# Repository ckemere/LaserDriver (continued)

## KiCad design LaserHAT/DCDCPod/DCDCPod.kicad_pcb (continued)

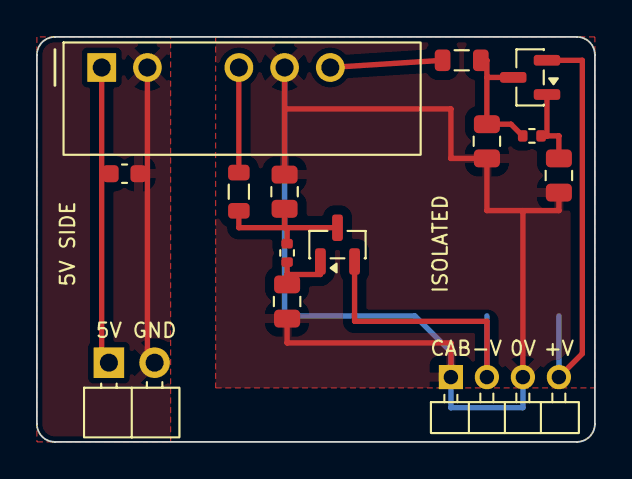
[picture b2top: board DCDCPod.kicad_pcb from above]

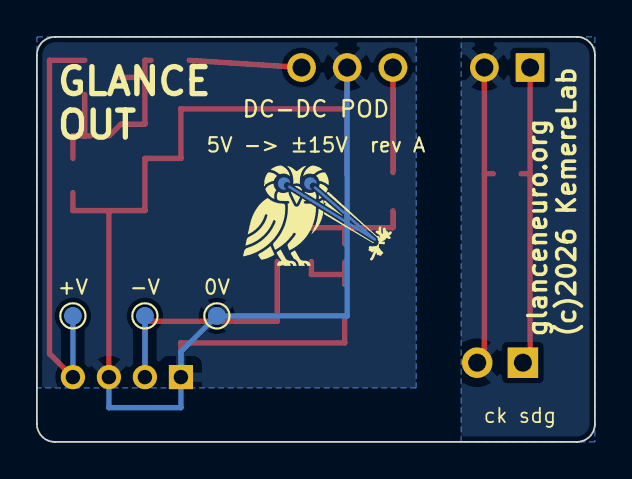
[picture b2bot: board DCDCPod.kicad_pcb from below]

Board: 2 copper layers, 31.0 x 22.5 mm, 18 parts (4 on the bottom side), 11 nets.

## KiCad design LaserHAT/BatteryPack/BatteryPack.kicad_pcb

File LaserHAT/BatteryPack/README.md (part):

# BatteryPack — ±V battery board for the e-stim module (rev D: series packs, floating charger)

Rev D, 2026-10-28.  One 100 × 100 mm board carries two off-the-shelf 4S hobby packs (any LiPo or Li-ion pack with the
standard JST-XH 5-pin balance plug and an XT60 discharge plug, 850–1550 mAh class, about 70–76 × 35 × 30–37 mm) strapped
to its underside, permanently in series, and gives the e-stim module +V / 0 V / −V (12.0–16.8 V per rail) on a 4-pin
JST-PH.  One USB-C PD charger floats on its own ground and a relay, run by a small MCU, switches it between the packs; one
toggle does ON / OFF.  2-layer, JLC assembled (toggle, XH and PH sockets, XT60s and the relay through-hole).

Rev C (commit `8b583b4`) charged the packs in parallel through a RUN / OFF / CHARGE toggle.  That made one half of the board
jump by a pack voltage between the modes, needed a PTC link and an equalising rule for mismatched packs, and left no single
reference for a ground pour.  Rev D fixes the pack topology and moves all the switching into the charger.  Rev B
(`6fa6e9d`) was a 4S 18650 board with clips, two of them stacked.  The output cable to the module is unchanged except that
its pin 4 is now an interlock.

Files: `gen_schematic.py` + `sch_parts.py` + `sch_symbols.py` (+ `sch_engine.py`) generate `BatteryPack.kicad_sch`
(deterministic UUIDs, like the e-stim module); `tools/netcheck.py` proves the drawing matches `sch_parts.py`;
`tools/make_bom.py` writes `bom_BatteryPack.csv`; `tools/make_footprints.py` writes `battpack.pretty/` (toggle, relay,
opto; the clip footprint is kept for rev B).  Board: `tools/board_init.py` (once), `tools/pcb_sync.py` (footprints and
nets from the netlist), `tools/place.py` (outline, slots, holes, placement, silk; idempotent) and `tools/autoroute.py`
(rip-up, stubs out of pads narrower than their net class, Freerouting headless through DSN/SES, stub clean-up, DRC) built
it — the user is remote, so the layout is scripted rather than hand-placed like the other boards.  Hand edits in pcbnew
are fine afterwards; re-running `place.py` + `autoroute.py` discards them.  `tools/stamp_fields.py` puts the LCSC codes on
the footprints, `tools/make_fab.py` writes `../fab/BatteryPack/` (gerbers, JLC BOM + CPL).  `firmware/` is the charge
controller's program (see below).

## What is on it

| Block | Parts | Notes |
|---|---|---|
| Pack sockets | per pack an XT60 and a JST-XH: J7 / J5 (pack A, −V side), J8 / J6 (pack B, +V side); XT60 = Amass XT60PW-M horizontal (C98732, ext), XH = JST S5B-XH-A-1 right-angle (C163038, ext) | the XT60 discharge plug carries the run and charge current (J7 = GND / 0V, J8 = 0V / +BATB; the plug is keyed, the footprint silk marks + and −); the balance plug gives the cell taps (XH pin 1 = black = pack negative, 2–4 = taps, 5 = pack positive; pins 1 and 5 parallel the XT60).  J5 = GND, C1, C2, C3, 0V; J6 = 0V, B1, B2, B3, +BATB.  **0V = pack A's positive = pack B's negative = the output reference, always.**  A pack with an XT30 lead needs an XT30-to-XT60 adapter |
| Balancers | pack A: U6–U9 HY2213-BB3A (C113632, ext), Q7–Q10 AO3400A, R35–R38 100 R 1206, R31–R34, C12–C15; pack B: U10–U13, Q15–Q18, R62–R65, R58–R61, C16–C19 | 42 mA bleed above 4.200 V, release 4.19 V, 2.5 µA standing, per cell of both packs |
| Toggle | SW1 MTS-202 DPDT ON-ON (C55159891, ext; **JLC stock 195 on 2026-10-28**) | **ON / OFF**.  Pole 1 (common EN_A): ON → 0V.  Pole 2 (common EN_B): ON → +BATB.  OFF opens both: outputs off, gauges dark (R40 / R82 hold the enables low) |
| +V chain (pack B) | F1 100 mA PTC MF-MSMF010-2 (C12430, ext), Q1 AO3401A, R1/R2 100k, Q22 2N7002, R81 1M, U15B (LM393), R53 1M | +BATB → F1 → +SW → Q1 → +OUT (J3.1).  Q22 pulls Q1's gate low while ENB_G (= EN_B through R81) is high **and its source, J3.4, is at 0V** — the module's plug straps pin 4 to pin 2, so +V can only appear with 0V connected.  U15B pulls ENB_G low below 12.0 V (back above 12.8 V), the opto U17 pulls it low while a brick is plugged in |
| −V chain (pack A) | F2 100 mA PTC, Q11 AO3400A (N, in pack A's negative), R39/R40 100k, U2B (LM393), R11 470k, Q14 + D1 (ON) | GND → F2 → Q11 → −V (J3.3).  Q11's gate is pack A / 2 from EN_A (= 0V when ON); U2B pulls it low below 12.0 V, back on above 12.9 V.  −V alone is harmless to the module (nothing in it conducts without 0V), so chain A is not interlocked.  Q14 lights D1 while Q11 conducts |
| Gauge rails | Q20 AO3401A + R77/R78 + Q21 2N7002 + R79/R80 (+G = 0V through Q20); Q23 + R83/R84 + Q24 (+GB = +BATB through Q23) | both rails follow EN_A / EN_B only: the gauges show whenever the toggle is ON, charging or not |
| Gauges | pack A: U3 CJ431, R3–R10, U1/U2 LM393, D2–D4 + R13–R15 on +G; pack B: U16, R45–R52, U14/U15, D12–D14 + R55–R57 on +GB, D11 + R54 ON from +OUT | per pack: green ≥ 15.9 V, green ≥ 15.1 V, yellow ≥ 14.3 V, ~1 mA each (the ladder's R4 / R46 is 6.2k now that the rail is the pack itself, not the pack − 0.25 V) |
| Charging interlock | U17 EL817S1 opto (C2912100, ext), R76 10k | LED from the island's VBUS; transistor holds ENB_G at 0V → +V off (and the module's fault line reports it) whenever a brick is in, so the brick's mains leakage can never reach the electrode |
| **Charger island** (floats on CGND) | J1 USB-C (C165948, ext), U4 CH224A (C42459160, ext) + C3 + R24 120k, U18 TLV76033 LDO (C2683368, ext) + C22/C23, **Q13 AO3401A VBUS switch** + R43/R44 + C28 10n (0.5 ms soft start) + Q12 2N7002 + R42, U5 CN3704 (C51659, ext), Q6 AO3401A, D7/D8 SS34, L1 33 µH (C408454, ext; CN3704 table 2 for 1 A at 20 V in; LCSC's own site does not list this code but JLC's parts search does, 10 k in stock, as for the 22 µH C408453 before), R25+R26 0.2 R, C4–C11, R27, RT1 NTC (C13564, ext), R28/R29 10k | PD brick negotiated to 20 V (the CH224A's DP / DM stay open: the USB data lines belong to the MCU).  Q13 passes VBUS to the charger only while the MCU drives CHG_EN; the charger's output +CHG / CGND goes to the relay.  1 A CC into one pack at a time, 16.8 V ±1 % CV, termination 92 mA, trickle 150 mA below 11.2 V, re-charge below 16.0 V, 18.1 V over-voltage cut, NTC stops it hot / cold.  The island is the only part of the board whose potential moves (it rides on GND or on 0V); the brick is mains-isolated, so that is fine.  **Up to 2 A:** R25 + R26 = 0.1 R, L1 20 µH, a 45 W brick (the HFD2's contacts are rated 2 A) |
| Relays | K1 Omron G6S-2 DC12 (C1525289, ext), R86 680 R 1206, Q19 2N7002, R85 100k, D19 1N4148W; **K2 LINK**: the same relay (R88, Q25, R87, D20), both poles NO in series with the island's +CHG and CGND | 12 V coils (1028 Ω) fed from VBUS through 680 R: 11.7 mA, 12 V on the coil at 20 V, must-operate 9 V (the 24 V HFD2 of the first draft had a ≤ 18 V pick-up against a 20 V bus minus cable drop: no margin).  Pin 1 = coil +, 12 = coil −; D19 flyback across the coil; R85 holds Q19 off while the MCU is in reset / DFU.  DPDT 2 A: released = pack A (NC 3 / 10: +CHG → 0V, CGND → GND), energised = pack B (NO 5 / 8: +CHG → +BATB, CGND → 0V).  Only ever switched with the charger off **and with K2 open**: a DPDT's two poles are not guaranteed to transfer together, and with the island still tied to one pack the mismatched intermediate states (+CHG on +BATB with CGND on GND, or both on 0V) would put 33.6 V across the charger (C7 / C8 25 V, CN3704 BAT 28 V abs max) or short C7 / C8 through the contacts; so the MCU opens K2, moves K1, closes K2 (30 ms each; G6S-2 operate / release ≤ 5 ms).  K2 is also open whenever the MCU is unpowered or idle, so the island is off both packs then (no idle drain, nothing lifted by leakage through D7 / Q6) |
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
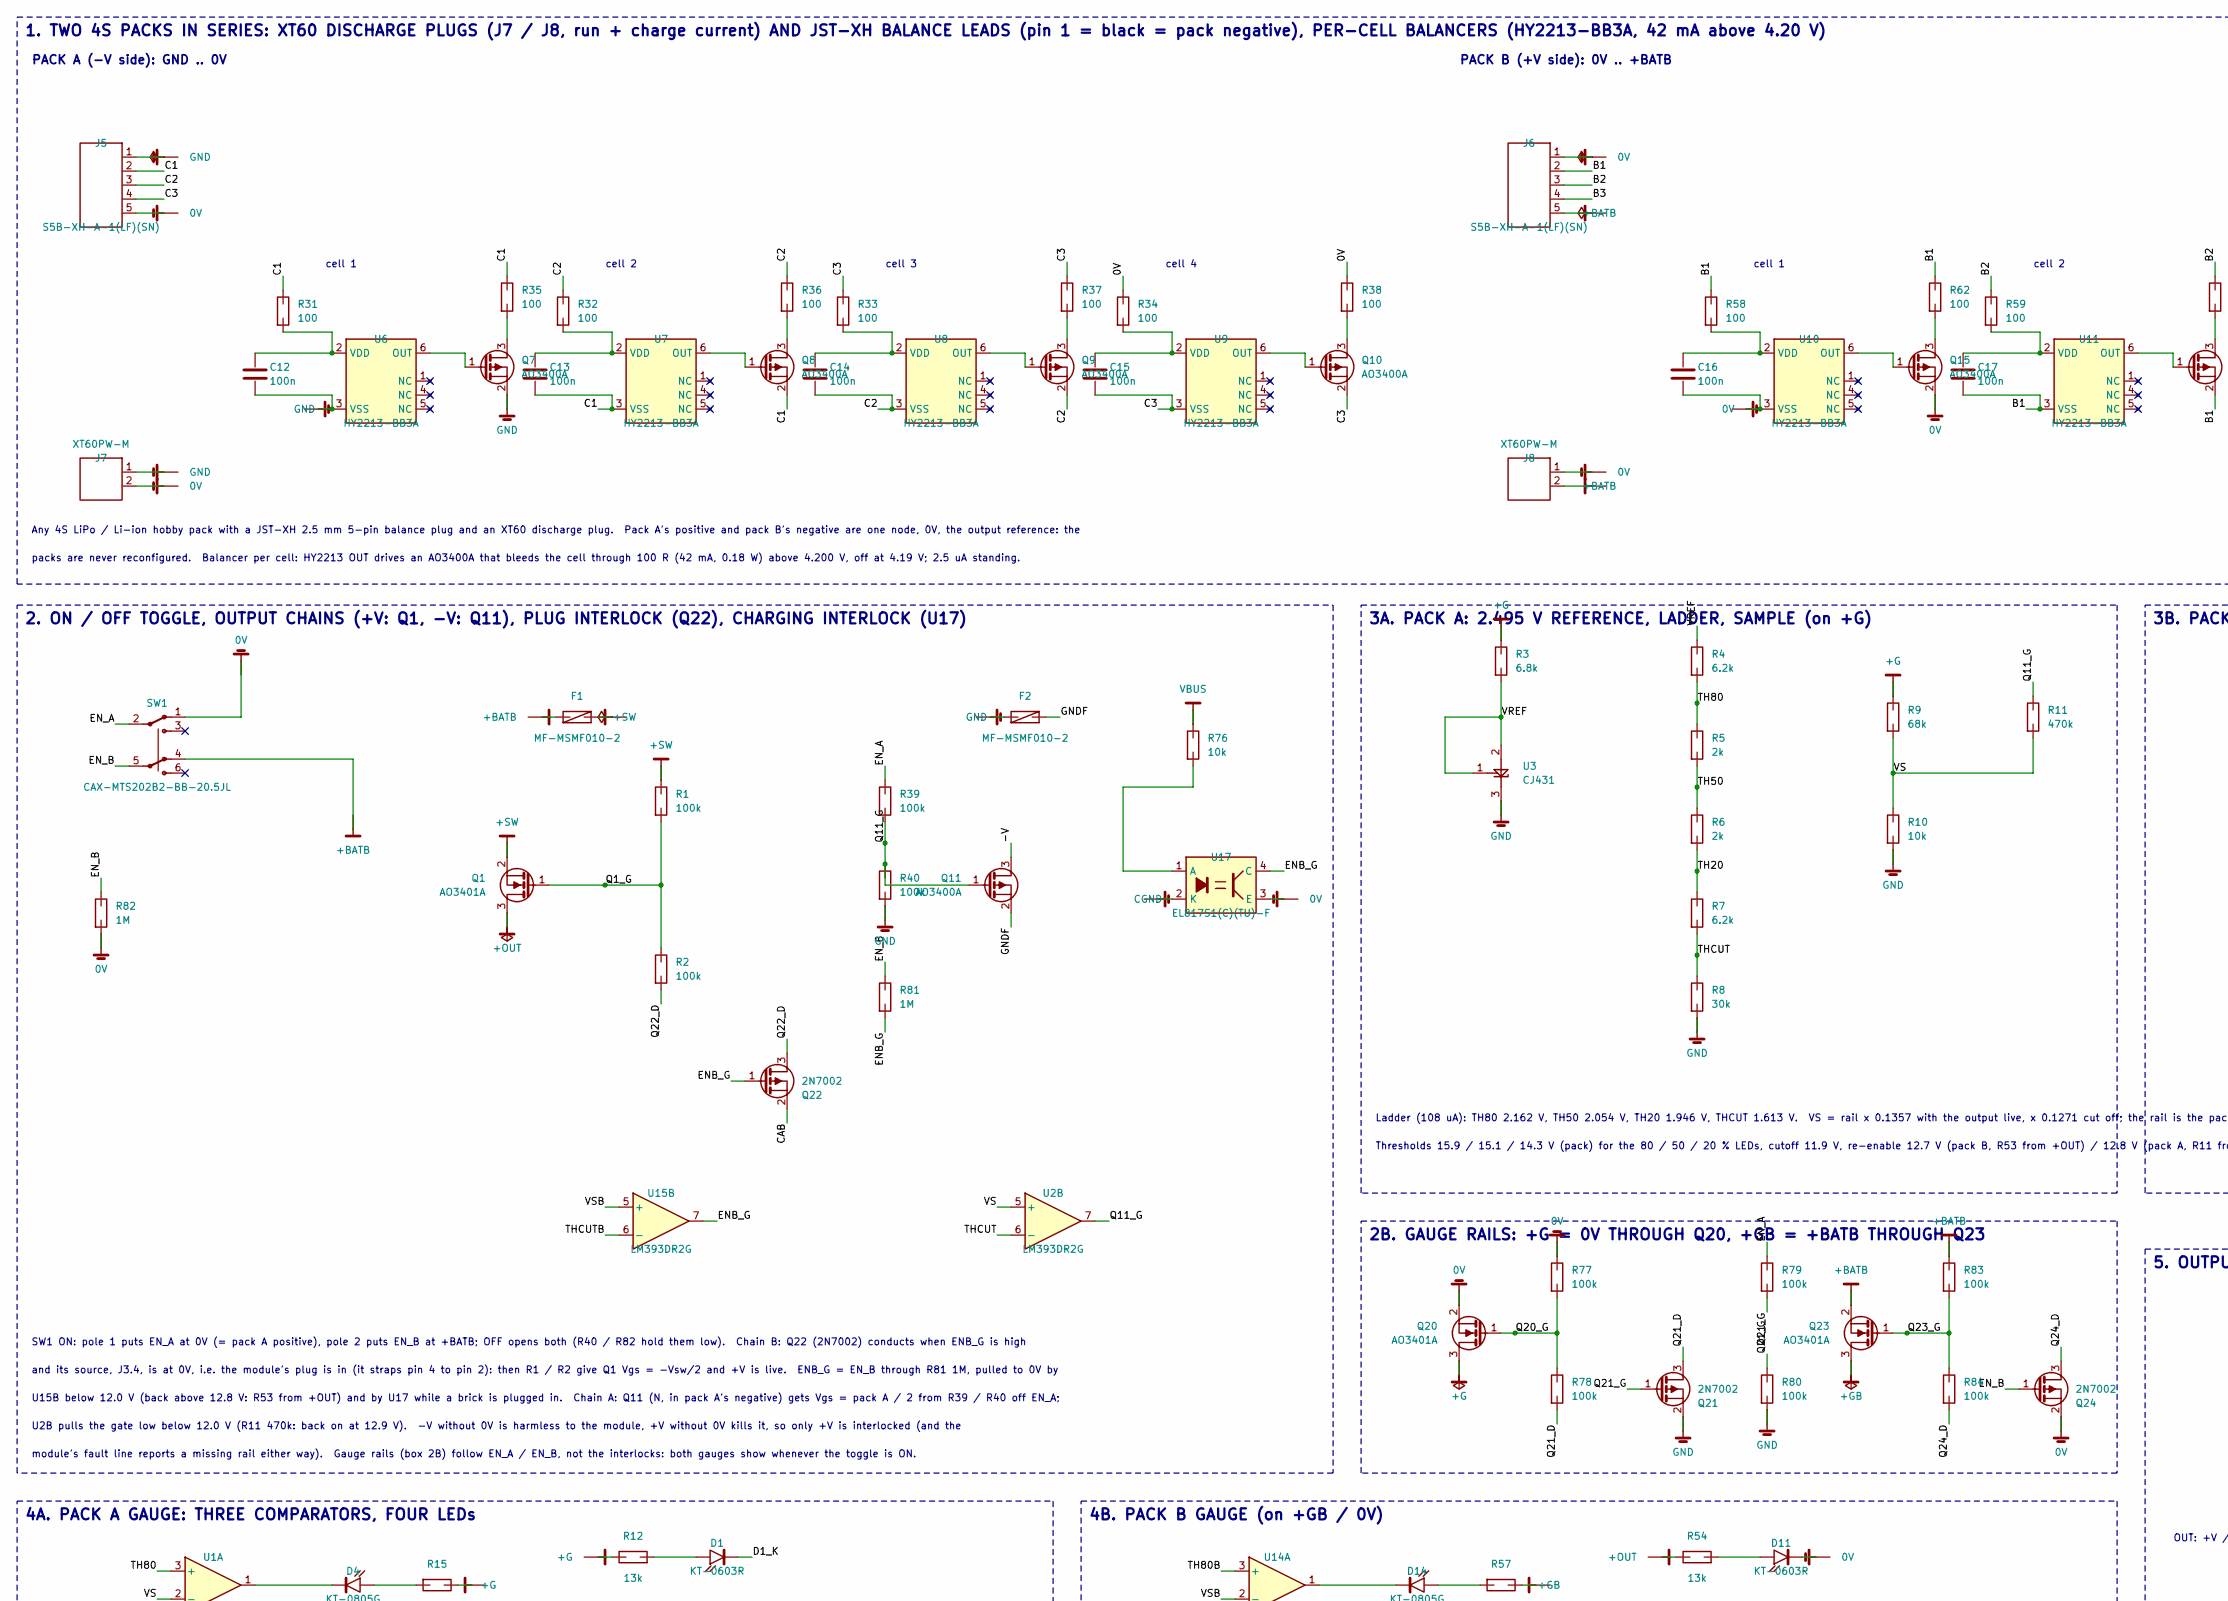
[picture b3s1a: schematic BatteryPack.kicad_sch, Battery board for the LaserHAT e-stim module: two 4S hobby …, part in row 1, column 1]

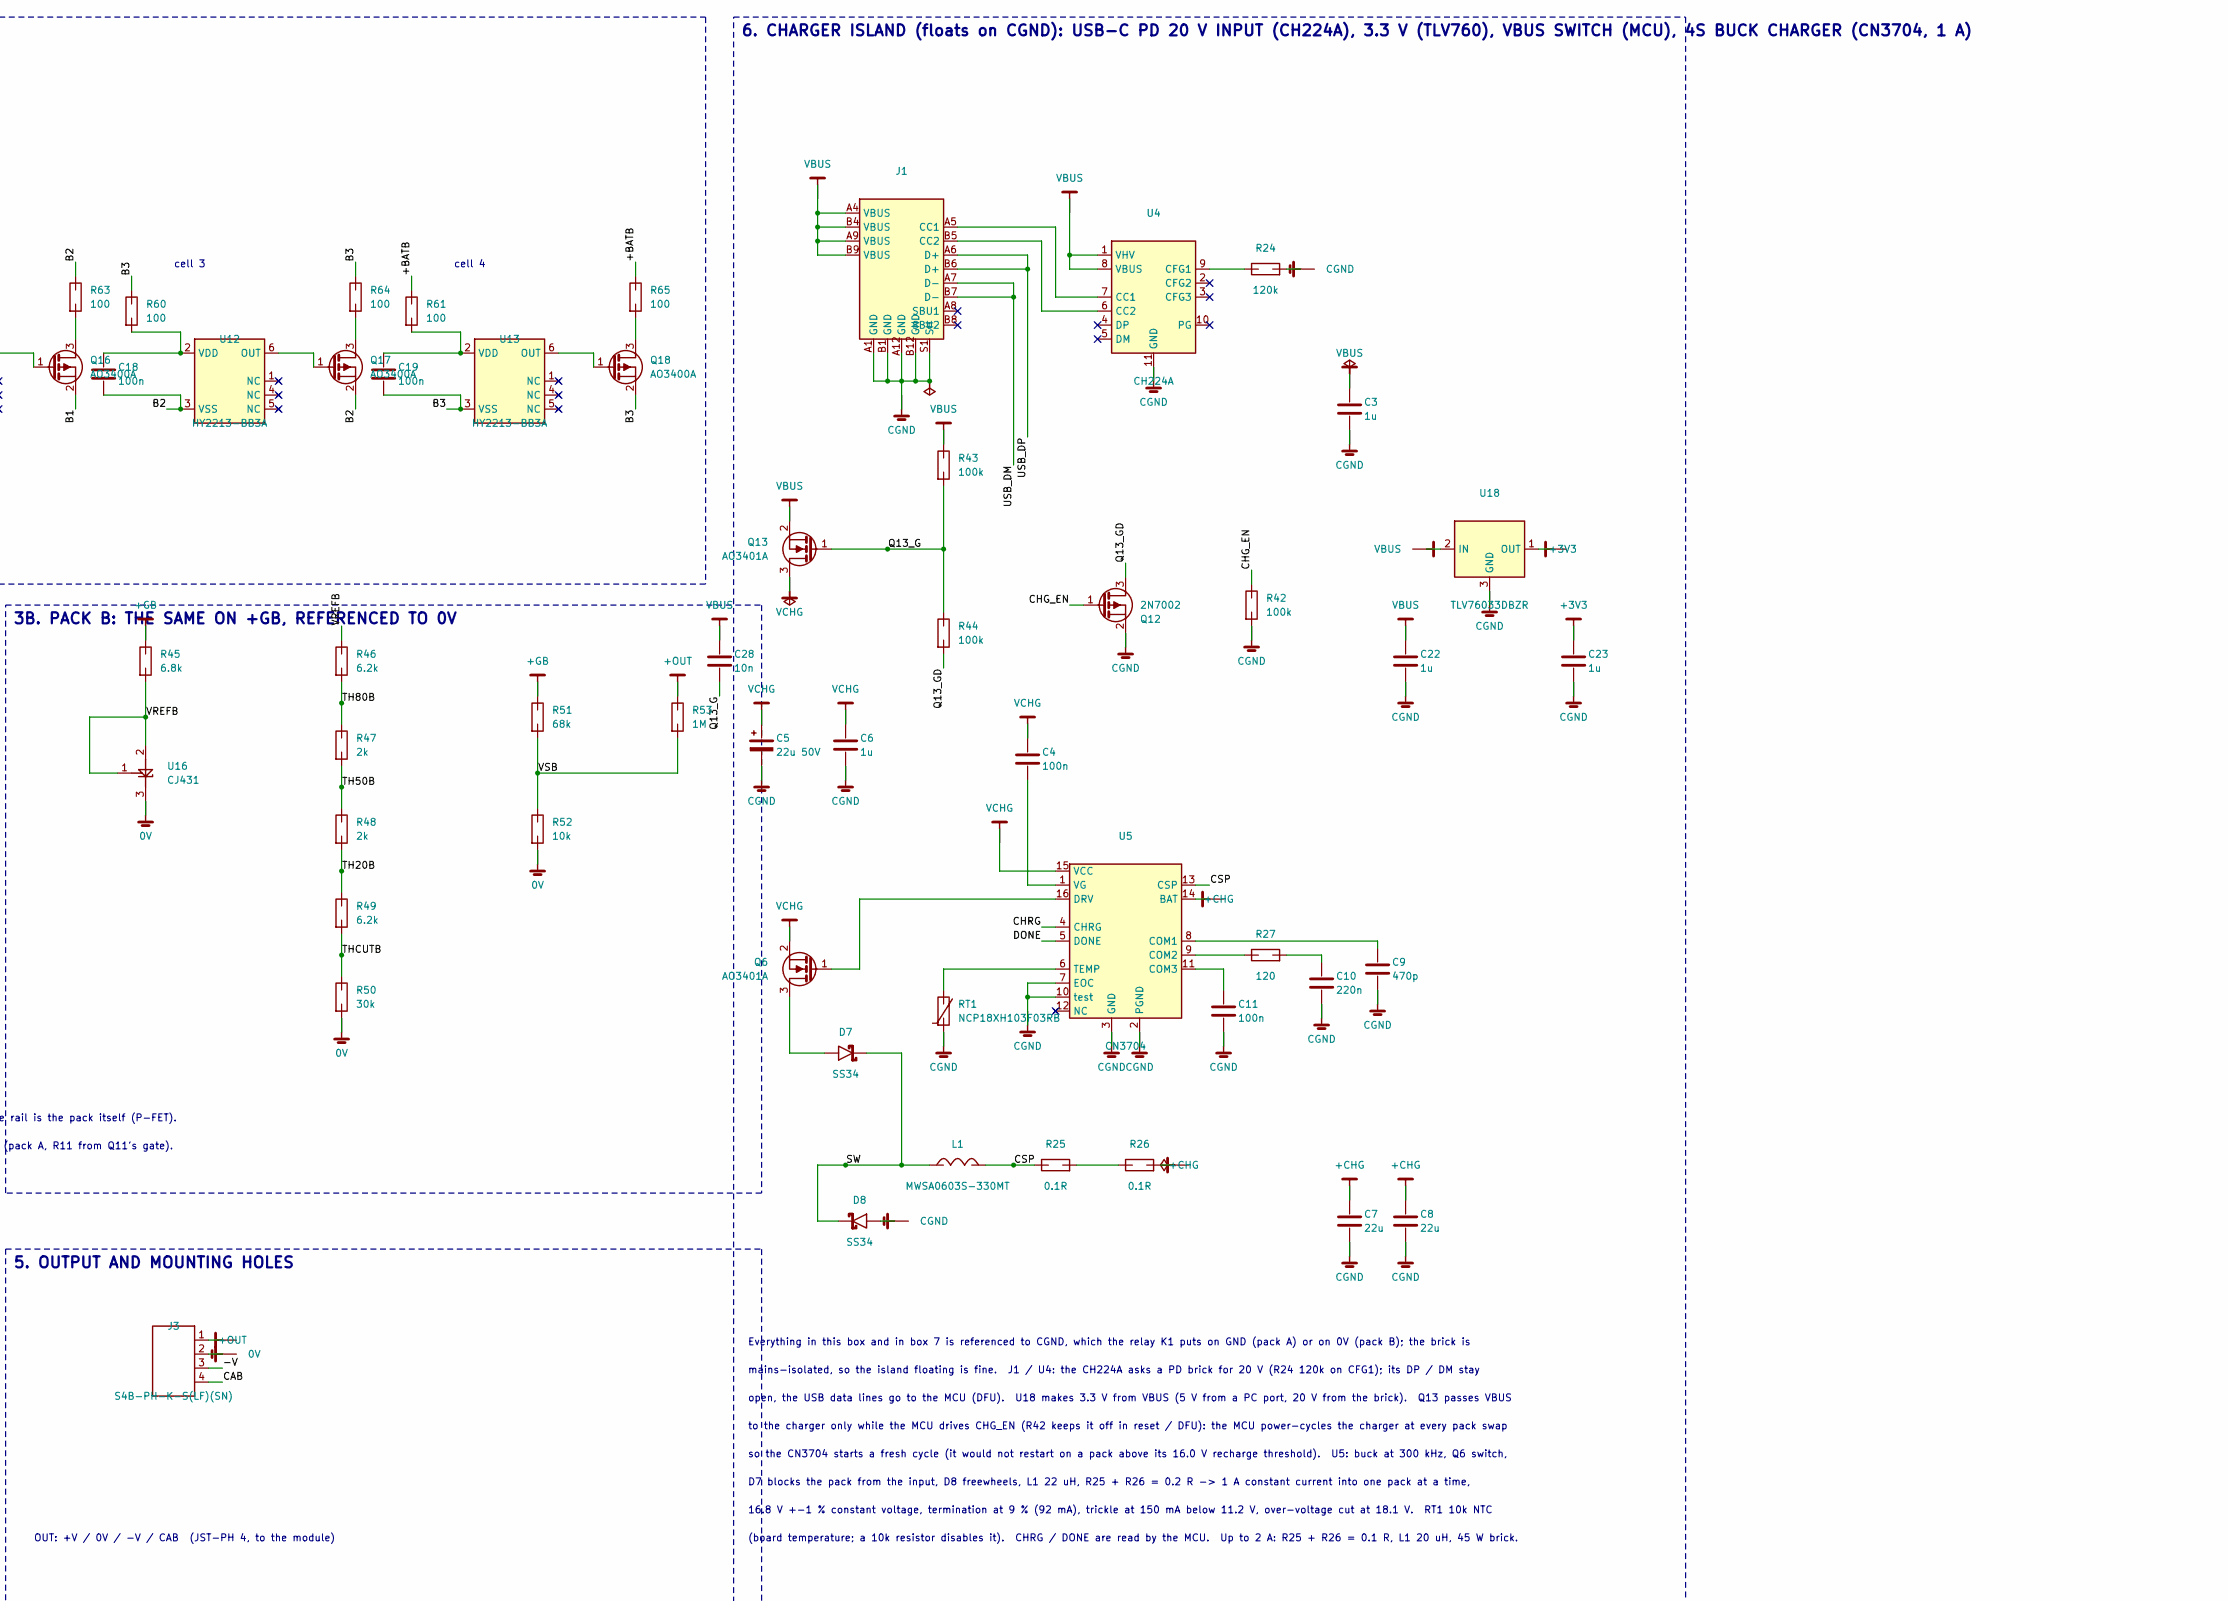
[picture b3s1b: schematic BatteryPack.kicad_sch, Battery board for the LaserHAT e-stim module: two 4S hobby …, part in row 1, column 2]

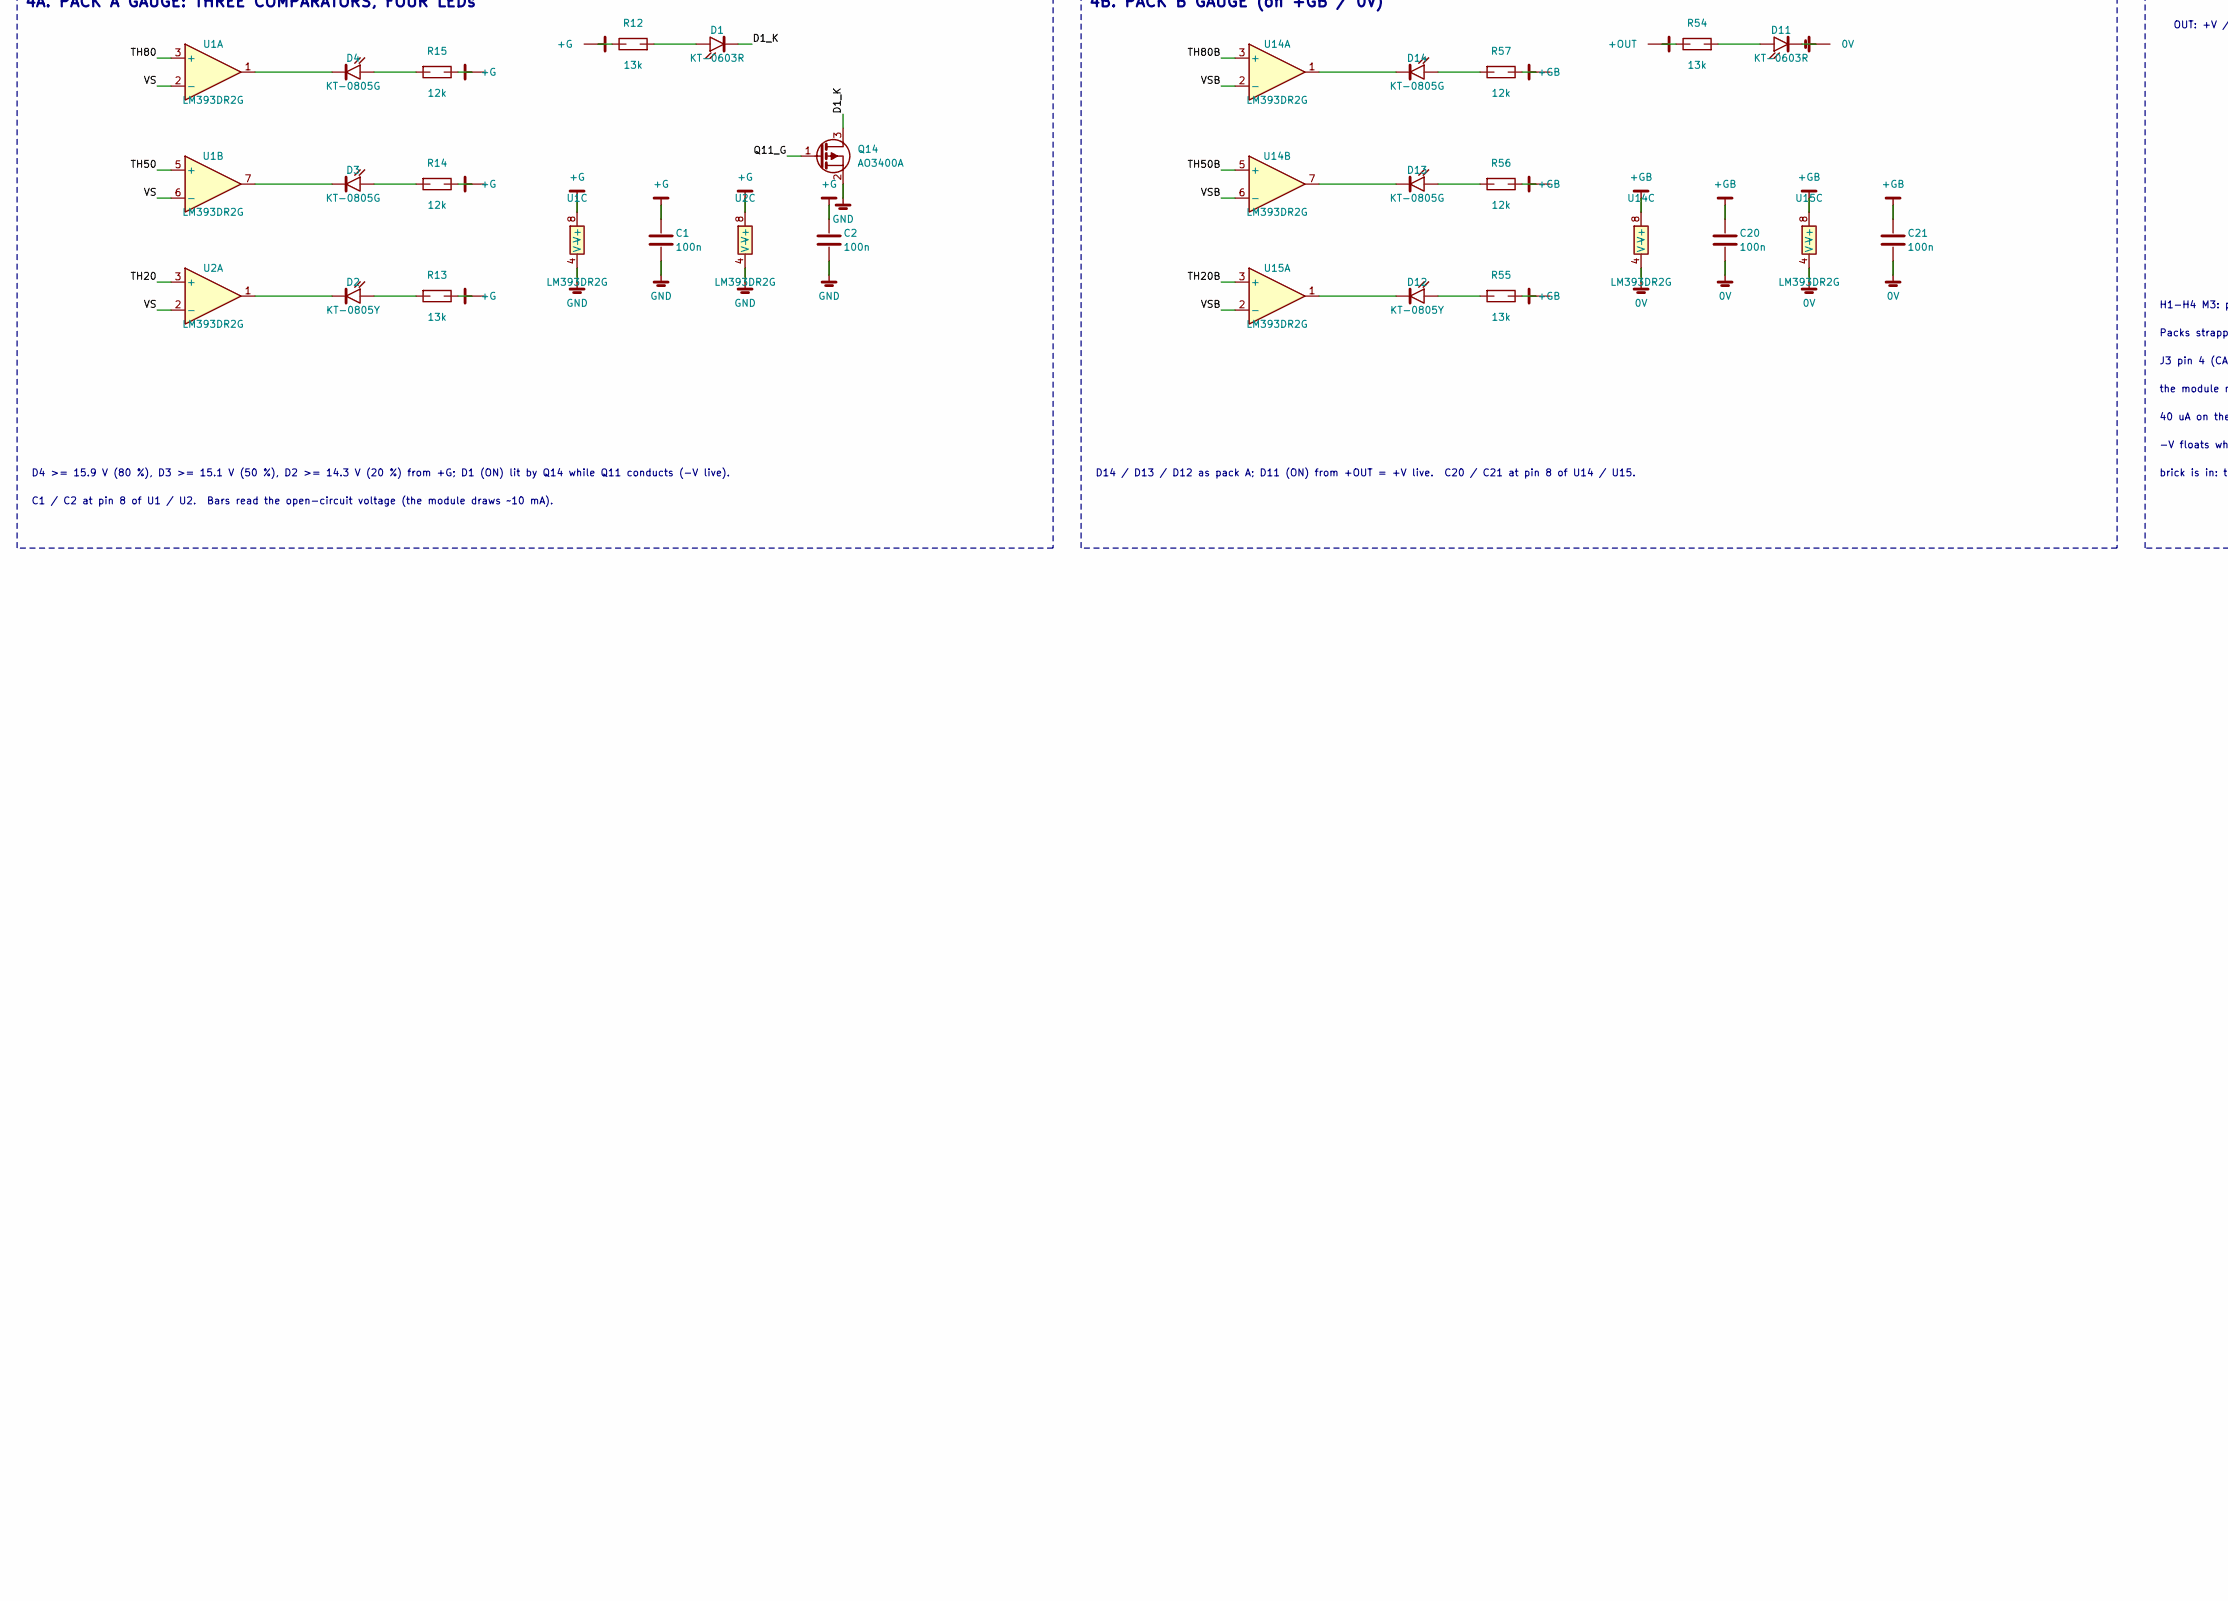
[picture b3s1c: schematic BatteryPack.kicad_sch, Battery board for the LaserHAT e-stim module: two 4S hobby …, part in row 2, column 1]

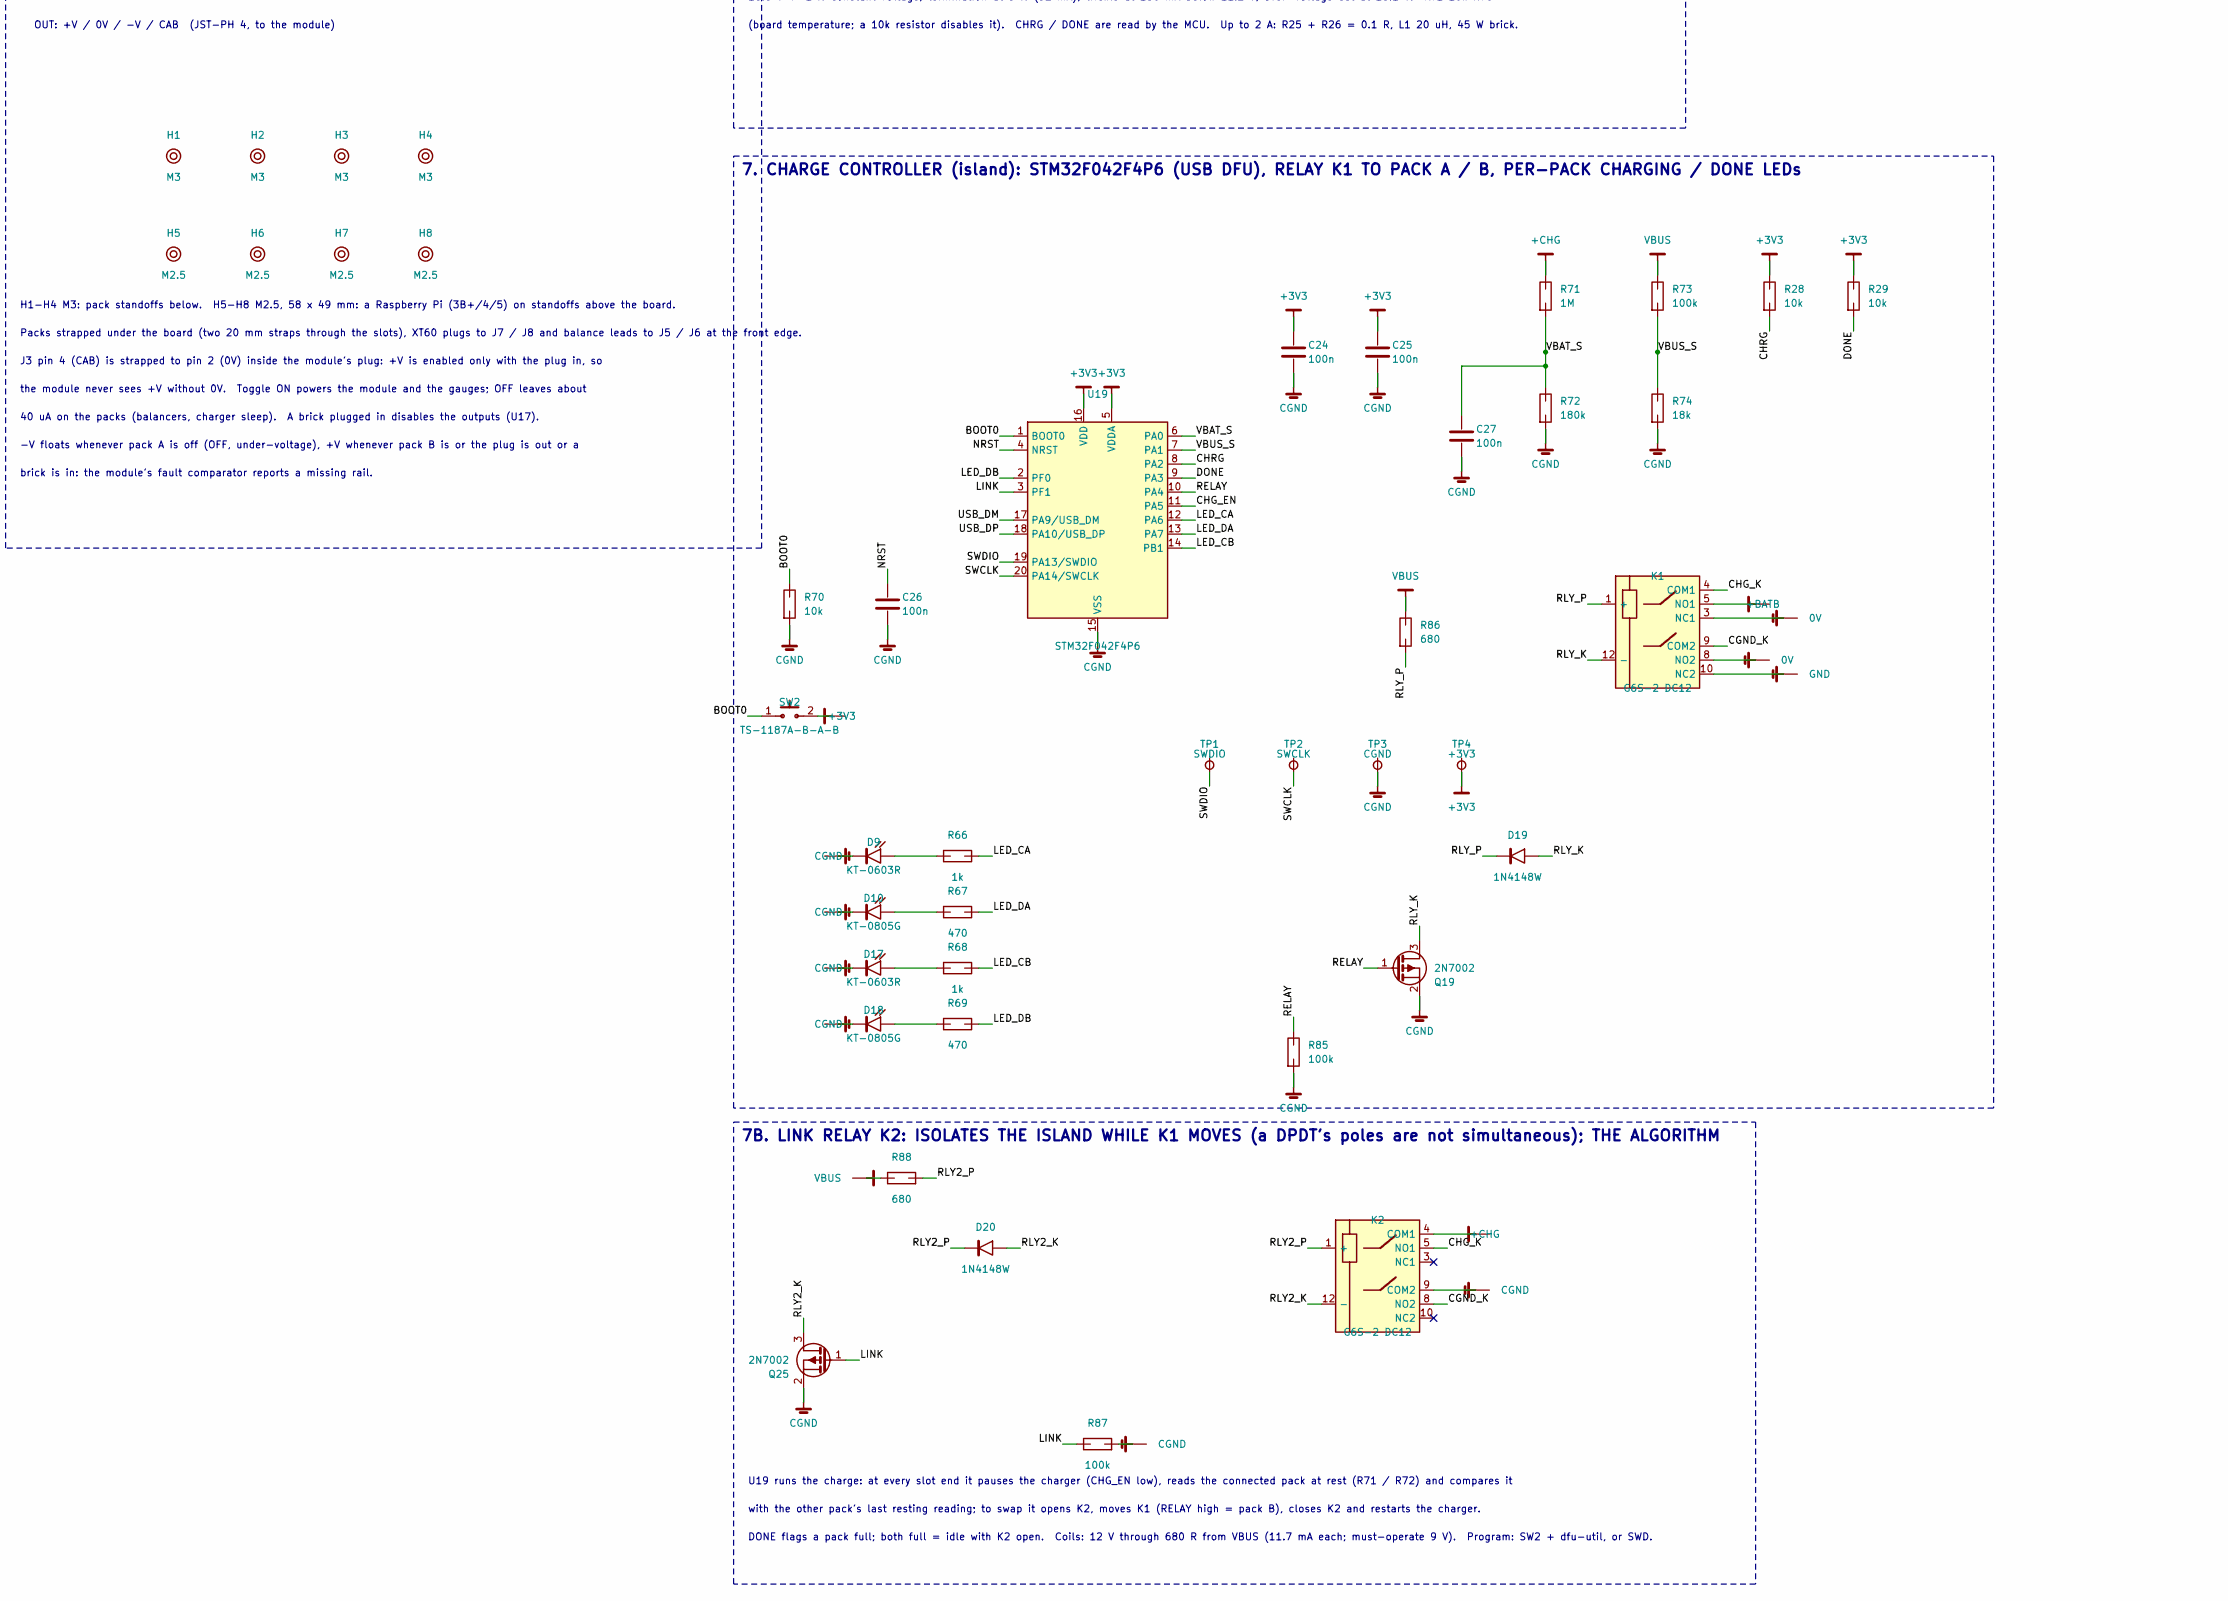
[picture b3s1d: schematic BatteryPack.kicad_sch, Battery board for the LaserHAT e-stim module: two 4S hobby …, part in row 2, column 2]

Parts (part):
C1, C2, C4, C11, C12, C13, C14, C15, C16, C17, C18, C19, C20, C21, C24, C25, C26, C27: 100n; C_0603_1608Metric; LCSC Part # C14663
C3, C6, C22, C23: 1u; C_0603_1608Metric; LCSC Part # C15849
C5: 22u 50V; CP_Elec_6.3x5.4; LCSC Part # C2836438
C7, C8: 22u; C_1206_3216Metric; LCSC Part # C12891
C9: 470p; C_0603_1608Metric; LCSC Part # C1620
C10: 220n; C_0603_1608Metric; LCSC Part # C21120
C28: 10n; C_0603_1608Metric; LCSC Part # C57112
D1, D9, D11, D17: KT-0603R; LED_0603_1608Metric; LCSC Part # C2286
D2, D12: KT-0805Y; LED_0805_2012Metric; LCSC Part # C2296
D3, D4, D10, D13, D14, D18: KT-0805G; LED_0805_2012Metric; LCSC Part # C2297
D7, D8: SS34; D_SMA; LCSC Part # C8678
D19, D20: 1N4148W; D_SOD-123; LCSC Part # C81598
F1, F2: MF-MSMF010-2; Fuse_1812_4532Metric; LCSC Part # C12430
H1, H2, H3, H4: M3; MountingHole_3.2mm_M3
H5, H6, H7, H8: M2.5; MountingHole_2.7mm_M2.5
J1: TYPE-C-31-M-12; USB_C_Receptacle_HRO_TYPE-C-31-M-12; LCSC Part # C165948
J3: S4B-PH-K-S(LF)(SN); JST_PH_S4B-PH-K_1x04_P2.00mm_Horizontal; LCSC Part # C157926
J5, J6: S5B-XH-A-1(LF)(SN); JST_XH_S5B-XH-A-1_1x05_P2.50mm_Horizontal; LCSC Part # C163038
J7, J8: XT60PW-M; LCSC Part # C98732
K1, K2: G6S-2 DC12; Relay_DPDT_Omron_G6S-2; LCSC Part # C1525289
L1: MWSA0603S-330MT; L_Sunlord_MWSA0603S; LCSC Part # C408454
Q1, Q6, Q13, Q20, Q23: AO3401A; SOT-23; LCSC Part # C15127
Q7, Q8, Q9, Q10, Q11, Q14, Q15, Q16, Q17, Q18: AO3400A; SOT-23; LCSC Part # C20917
Q12, Q19, Q21, Q22, Q24, Q25: 2N7002; SOT-23; LCSC Part # C8545
R1, R2, R39, R40, R42, R43, R44, R73, R77, R78, R79, R80, R83, R84, R85, R87: 100k; R_0603_1608Metric; LCSC Part # C25803
R3, R45: 6.8k; R_0603_1608Metric; LCSC Part # C23212
R4, R7, R46, R49: 6.2k; R_0603_1608Metric; LCSC Part # C4260
R5, R6, R47, R48: 2k; R_0603_1608Metric; LCSC Part # C22975
R8, R50: 30k; R_0603_1608Metric; LCSC Part # C22984
R9, R51: 68k; R_0603_1608Metric; LCSC Part # C23231
R10, R28, R29, R52, R70, R76: 10k; R_0603_1608Metric; LCSC Part # C25804
R11: 470k; R_0603_1608Metric; LCSC Part # C23178
R12, R13, R54, R55: 13k; R_0603_1608Metric; LCSC Part # C22797
R14, R15, R56, R57: 12k; R_0603_1608Metric; LCSC Part # C22790
R24: 120k; R_0603_1608Metric; LCSC Part # C25808
R25, R26: 0.1R; R_1206_3216Metric; LCSC Part # C25334
R27: 120; R_0603_1608Metric; LCSC Part # C22787
R31, R32, R33, R34, R58, R59, R60, R61: 100; R_0603_1608Metric; LCSC Part # C22775
R35, R36, R37, R38, R62, R63, R64, R65: 100; R_1206_3216Metric; LCSC Part # C17901
R53, R71, R81, R82: 1M; R_0603_1608Metric; LCSC Part # C22935
R66, R68: 1k; R_0603_1608Metric; LCSC Part # C21190
R67, R69: 470; R_0603_1608Metric; LCSC Part # C23179
R72: 180k; R_0603_1608Metric; LCSC Part # C22827
R74: 18k; R_0603_1608Metric; LCSC Part # C25810
R86, R88: 680; R_1206_3216Metric; LCSC Part # C17975
RT1: NCP18XH103F03RB; R_0603_1608Metric; LCSC Part # C13564
SW1: CAX-MTS202B2-BB-20.5JL; SW_MTS-202; LCSC Part # C55159891
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
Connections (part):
0V: C16.2, C20.2, C21.2, D11.1 (K), J3.2, J5.5, J6.1, J7.2, J8.1, K1.3 (NC1), K1.8 (NO2), Q15.2 (S), Q20.2 (S), Q24.2 (S), R34.1, R38.1, R50.2, R52.2, R77.1, R82.2, SW1.1 (A1), U10.3 (VSS), U14.4 (V-), U15.4 (V-), U16.3 (A), U17.3 (E)
+3V3: C23.1, C24.1, C25.1, R28.1, R29.1, SW2.2, TP4.1, U18.1 (OUT), U19.5 (VDDA), U19.16 (VDD)
+BATB: F1.1, J6.5, J8.2, K1.5 (NO1), Q23.2 (S), R61.1, R65.1, R83.1, SW1.4 (A2)
+CHG: C7.1, C8.1, K2.4 (COM1), R26.2, R71.1, U5.14 (BAT)
+G: C1.1, C2.1, Q20.3 (D), R3.1, R9.1, R12.1, R13.1, R14.1, R15.1, U1.8 (V+), U2.8 (V+)
+GB: C20.1, C21.1, Q23.3 (D), R45.1, R51.1, R55.1, R56.1, R57.1, U14.8 (V+), U15.8 (V+)
+OUT: J3.1, Q1.3 (D), R53.1, R54.1
+SW: F1.2, Q1.2 (S), R1.1
/-V: J3.3, Q11.3 (D)
/B1: C17.2, J6.2, Q16.2 (S), R58.1, R62.1, U11.3 (VSS)
/B2: C18.2, J6.3, Q17.2 (S), R59.1, R63.1, U12.3 (VSS)
/B3: C19.2, J6.4, Q18.2 (S), R60.1, R64.1, U13.3 (VSS)
/BOOT0: R70.1, SW2.1, U19.1 (BOOT0)
/C1: C13.2, J5.2, Q8.2 (S), R31.1, R35.1, U7.3 (VSS)
/C2: C14.2, J5.3, Q9.2 (S), R32.1, R36.1, U8.3 (VSS)
/C3: C15.2, J5.4, Q10.2 (S), R33.1, R37.1, U9.3 (VSS)
/CAB: J3.4, Q22.2 (S)
/CGND_K: K1.9 (COM2), K2.8 (NO2)
/CHG_EN: Q12.1 (G), R42.1, U19.11 (PA5)
/CHG_K: K1.4 (COM1), K2.5 (NO1)
/CHRG: R28.2, U5.4 (CHRG), U19.8 (PA2)
/CSP: L1.2, R25.1, U5.13 (CSP)
/D1_K: D1.1 (K), Q14.3 (D)
/DONE: R29.2, U5.5 (DONE), U19.9 (PA3)
/ENB_G: Q22.1 (G), R81.2, U15.7, U17.4 (C)
/EN_A: R39.1, R79.1, SW1.2 (C1)
/EN_B: Q24.1 (G), R81.1, R82.1, SW1.5 (C2)
/GNDF: F2.2, Q11.2 (S)
/LED_CA: R66.1, U19.12 (PA6)
/LED_CB: R68.1, U19.14 (PB1)
/LED_DA: R67.1, U19.13 (PA7)
/LED_DB: R69.1, U19.2 (PF0)
/LINK: Q25.1 (G), R87.1, U19.3 (PF1)
/NRST: C26.1, U19.4 (NRST)
/Q1_G: Q1.1 (G), R1.2, R2.1
/Q11_G: Q11.1 (G), Q14.1 (G), R11.1, R39.2, R40.1, U2.7
/Q13_G: C28.2, Q13.1 (G), R43.2, R44.1
/Q13_GD: Q12.3 (D), R44.2
/Q20_G: Q20.1 (G), R77.2, R78.1
/Q21_D: Q21.3 (D), R78.2
/Q21_G: Q21.1 (G), R79.2, R80.1
/Q22_D: Q22.3 (D), R2.2
/Q23_G: Q23.1 (G), R83.2, R84.1
/Q24_D: Q24.3 (D), R84.2
/RELAY: Q19.1 (G), R85.1, U19.10 (PA4)
/RLY2_K: D20.2 (A), K2.12 (-), Q25.3 (D)
/RLY2_P: D20.1 (K), K2.1 (+), R88.2
/RLY_K: D19.2 (A), K1.12 (-), Q19.3 (D)
/RLY_P: D19.1 (K), K1.1 (+), R86.2
/SW: D7.1 (K), D8.1 (K), L1.1
/SWCLK: TP2.1, U19.20 (PA14/SWCLK)
/SWDIO: TP1.1, U19.19 (PA13/SWDIO)
/TH20: R6.2, R7.1, U2.3 (+)
/TH20B: R48.2, R49.1, U15.3 (+)
/TH50: R5.2, R6.1, U1.5 (+)
/TH50B: R47.2, R48.1, U14.5 (+)
/TH80: R4.2, R5.1, U1.3 (+)
/TH80B: R46.2, R47.1, U14.3 (+)
/THCUT: R7.2, R8.1, U2.6 (-)
/THCUTB: R49.2, R50.1, U15.6 (-)
/USB_DM: J1.A7 (D-), J1.B7 (D-), U19.17 (PA9/USB_DM)
/USB_DP: J1.A6 (D+), J1.B6 (D+), U19.18 (PA10/USB_DP)
/VBAT_S: C27.1, R71.2, R72.1, U19.6 (PA0)
/VBUS_S: R73.2, R74.1, U19.7 (PA1)
/VREF: R3.2, R4.1, U3.1 (REF), U3.2 (K)
/VREFB: R45.2, R46.1, U16.1 (REF), U16.2 (K)
/VS: R9.2, R10.1, R11.2, U1.2 (-), U1.6 (-), U2.2 (-), U2.5 (+)
/VSB: R51.2, R52.1, R53.2, U14.2 (-), U14.6 (-), U15.2 (-), U15.5 (+)
CGND: C3.2, C5.2 (-), C6.2, C7.2, C8.2, C9.2, C10.2, C11.2, C22.2, C23.2, C24.2, C25.2, C26.2, C27.2, D8.2 (A), D9.1 (K), D10.1 (K), D17.1 (K), D18.1 (K), J1.A1 (GND), J1.A12 (GND), J1.B1 (GND), J1.B12 (GND), J1.S1 (SH), K2.9 (COM2), Q12.2 (S), Q19.2 (S), Q25.2 (S), R24.2, R42.2, R70.2, R72.2, R74.2, R85.2, R87.2, RT1.2, TP3.1, U4.11 (GND), U5.2 (PGND), U5.3 (GND), U5.7 (EOC), U5.10 (test), U17.2 (K), U18.3 (GND), U19.15 (VSS)
GND: C1.2, C2.2, C12.2, F2.1, J5.1, J7.1, K1.10 (NC2), Q7.2 (S), Q14.2 (S), Q21.2 (S), R8.2, R10.2, R40.2, R80.2, U1.4 (V-), U2.4 (V-), U3.3 (A), U6.3 (VSS)
unnamed: C10.1, R27.2
unnamed: D1.2 (A), R12.2
unnamed: D2.2 (A), R13.2
unnamed: D2.1 (K), U2.1
unnamed: D3.2 (A), R14.2
unnamed: D3.1 (K), U1.7
unnamed: D4.2 (A), R15.2
unnamed: D4.1 (K), U1.1
unnamed: D7.2 (A), Q6.3 (D)
unnamed: D9.2 (A), R66.2
unnamed: D10.2 (A), R67.2
unnamed: D11.2 (A), R54.2
unnamed: D12.2 (A), R55.2
unnamed: D12.1 (K), U15.1
unnamed: D13.2 (A), R56.2
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
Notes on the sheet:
1. TWO 4S PACKS IN SERIES: XT60 DISCHARGE PLUGS (J7 / J8, run + charge current) AND JST-XH BALANCE LEADS (pin 1 = black = pack negative), PER-CELL BALANCERS (HY2213-BB3A, 42 mA above 4.20 V)
PACK A (-V side): GND .. 0V
cell 1
cell 2
cell 3
cell 4
PACK B (+V side): 0V .. +BATB
Any 4S LiPo / Li-ion hobby pack with a JST-XH 2.5 mm 5-pin balance plug and an XT60 discharge plug. Pack A's positive and pack B's negative are one node, 0V, the output reference: the
packs are never reconfigured. Balancer per cell: HY2213 OUT drives an AO3400A that bleeds the cell through 100 R (42 mA, 0.18 W) above 4.200 V, off at 4.19 V; 2.5 uA standing.
2. ON / OFF TOGGLE, OUTPUT CHAINS (+V: Q1, -V: Q11), PLUG INTERLOCK (Q22), CHARGING INTERLOCK (U17)
SW1 ON: pole 1 puts EN_A at 0V (= pack A positive), pole 2 puts EN_B at +BATB; OFF opens both (R40 / R82 hold them low). Chain B: Q22 (2N7002) conducts when ENB_G is high
and its source, J3.4, is at 0V, i.e. the module's plug is in (it straps pin 4 to pin 2): then R1 / R2 give Q1 Vgs = -Vsw/2 and +V is live. ENB_G = EN_B through R81 1M, pulled to 0V by
U15B below 12.0 V (back above 12.8 V: R53 from +OUT) and by U17 while a brick is plugged in. Chain A: Q11 (N, in pack A's negative) gets Vgs = pack A / 2 from R39 / R40 off EN_A;
U2B pulls the gate low below 12.0 V (R11 470k: back on at 12.9 V). -V without 0V is harmless to the module, +V without 0V kills it, so only +V is interlocked (and the
module's fault line reports a missing rail either way). Gauge rails (box 2B) follow EN_A / EN_B, not the interlocks: both gauges show whenever the toggle is ON.
2B. GAUGE RAILS: +G = 0V THROUGH Q20, +GB = +BATB THROUGH Q23
3A. PACK A: 2.495 V REFERENCE, LADDER, SAMPLE (on +G)
3B. PACK B: THE SAME ON +GB, REFERENCED TO 0V
Ladder (108 uA): TH80 2.162 V, TH50 2.054 V, TH20 1.946 V, THCUT 1.613 V. VS = rail x 0.1357 with the output live, x 0.1271 cut off; the rail is the pack itself (P-FET).
Thresholds 15.9 / 15.1 / 14.3 V (pack) for the 80 / 50 / 20 % LEDs, cutoff 11.9 V, re-enable 12.7 V (pack B, R53 from +OUT) / 12.8 V (pack A, R11 from Q11's gate).
4A. PACK A GAUGE: THREE COMPARATORS, FOUR LEDs
D4 >= 15.9 V (80 %), D3 >= 15.1 V (50 %), D2 >= 14.3 V (20 %) from +G; D1 (ON) lit by Q14 while Q11 conducts (-V live).
C1 / C2 at pin 8 of U1 / U2. Bars read the open-circuit voltage (the module draws ~10 mA).
4B. PACK B GAUGE (on +GB / 0V)
D14 / D13 / D12 as pack A; D11 (ON) from +OUT = +V live. C20 / C21 at pin 8 of U14 / U15.
5. OUTPUT AND MOUNTING HOLES
OUT: +V / 0V / -V / CAB (JST-PH 4, to the module)
H1-H4 M3: pack standoffs below. H5-H8 M2.5, 58 x 49 mm: a Raspberry Pi (3B+/4/5) on standoffs above the board.
Packs strapped under the board (two 20 mm straps through the slots), XT60 plugs to J7 / J8 and balance leads to J5 / J6 at the front edge.
J3 pin 4 (CAB) is strapped to pin 2 (0V) inside the module's plug: +V is enabled only with the plug in, so
the module never sees +V without 0V. Toggle ON powers the module and the gauges; OFF leaves about
40 uA on the packs (balancers, charger sleep). A brick plugged in disables the outputs (U17).
-V floats whenever pack A is off (OFF, under-voltage), +V whenever pack B is or the plug is out or a
brick is in: the module's fault comparator reports a missing rail.
6. CHARGER ISLAND (floats on CGND): USB-C PD 20 V INPUT (CH224A), 3.3 V (TLV760), VBUS SWITCH (MCU), 4S BUCK CHARGER (CN3704, 1 A)
Everything in this box and in box 7 is referenced to CGND, which the relay K1 puts on GND (pack A) or on 0V (pack B); the brick is
mains-isolated, so the island floating is fine. J1 / U4: the CH224A asks a PD brick for 20 V (R24 120k on CFG1); its DP / DM stay
open, the USB data lines go to the MCU (DFU). U18 makes 3.3 V from VBUS (5 V from a PC port, 20 V from the brick). Q13 passes VBUS
to the charger only while the MCU drives CHG_EN (R42 keeps it off in reset / DFU): the MCU power-cycles the charger at every pack swap
so the CN3704 starts a fresh cycle (it would not restart on a pack above its 16.0 V recharge threshold). U5: buck at 300 kHz, Q6 switch,
